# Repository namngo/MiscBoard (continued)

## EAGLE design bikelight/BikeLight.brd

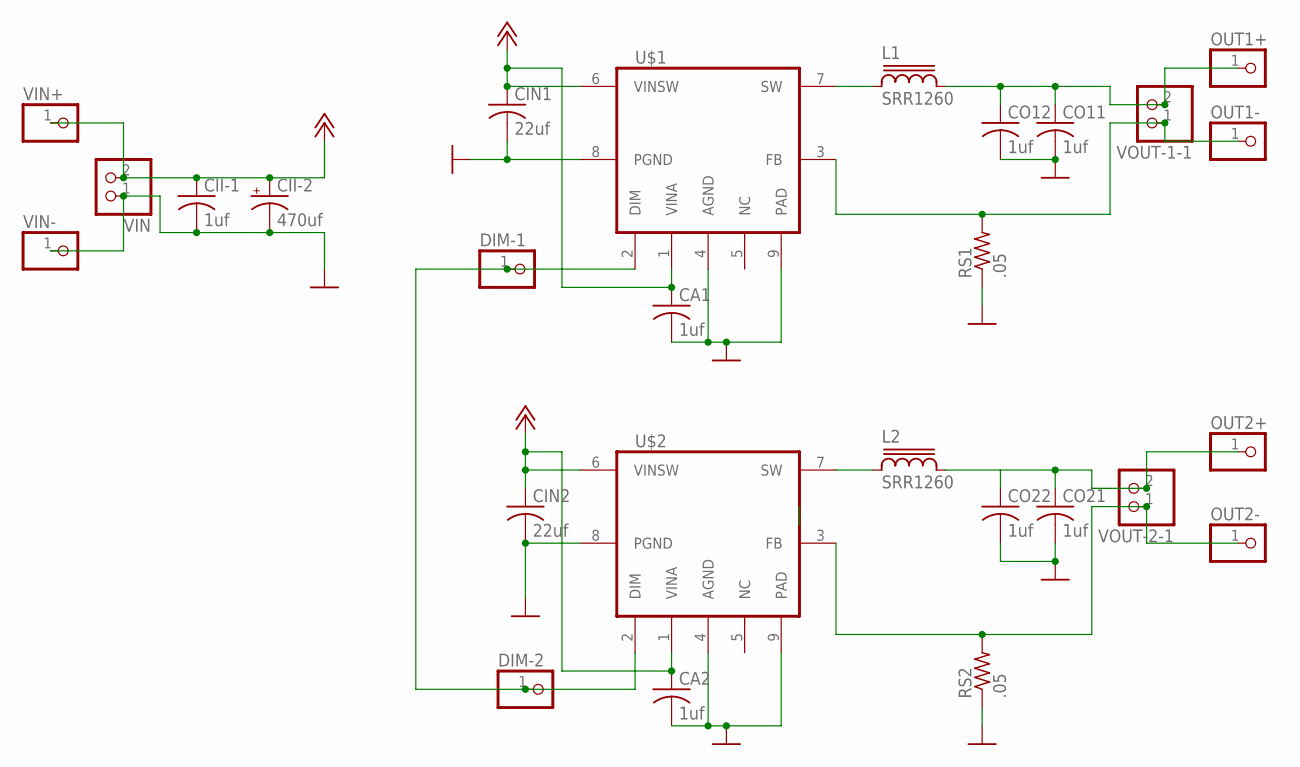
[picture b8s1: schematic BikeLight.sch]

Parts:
CA1, CA2: 1uf; C1210
CII-1: 1uf; C1210
CII-2: 470uf; UD-10X10_NICHICON
CIN1, CIN2: 22uf; C1210
CO11, CO12, CO21, CO22: 1uf; C1210
DIM-1, DIM-2: PINHD-1X1; 1X01
L1, L2: SRR1260
OUT1+, OUT1-, OUT2+, OUT2-: PINHD-1X1; 1X01
RS1, RS2: .05; R1206
U$1, U$2: LED2001PHR; SOIC127P600X170-9N
VIN: PINHD-1X2; 1X02
VIN+: PINHD-1X1; 1X01
VIN-: PINHD-1X1; 1X01
VOUT-1-1, VOUT-2-1: PINHD-1X2; 1X02

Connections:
+12V: CA1.1, CA2.1, CII-1.1, CII-2.+, CIN1.1, CIN2.1, U$1.1 (VINA), U$1.6 (VINSW), U$2.1 (VINA), U$2.6 (VINSW), VIN.2, VIN+.1
GND: CA1.2, CA2.2, CII-1.2, CII-2.-, CIN1.2, CIN2.2, CO11.2, CO12.2, CO21.2, CO22.2, RS1.1, RS2.1, U$1.4 (AGND), U$1.8 (PGND), U$1.9 (PAD), U$2.4 (AGND), U$2.8 (PGND), U$2.9 (PAD), VIN.1, VIN-.1
unnamed: DIM-1.1, DIM-2.1, U$1.2 (DIM), U$2.2 (DIM)
unnamed: L1.1, U$1.7 (SW)
unnamed: L2.1, U$2.7 (SW)
N-OUT-1-N: OUT1-.1, RS1.2, U$1.3 (FB), VOUT-1-1.1
N-OUT-1-P: CO11.1, CO12.1, L1.2, OUT1+.1, VOUT-1-1.2
N-OUT-2-N: OUT2-.1, RS2.2, U$2.3 (FB), VOUT-2-1.1
N-OUT-2-P: CO21.1, CO22.1, L2.2, OUT2+.1, VOUT-2-1.2

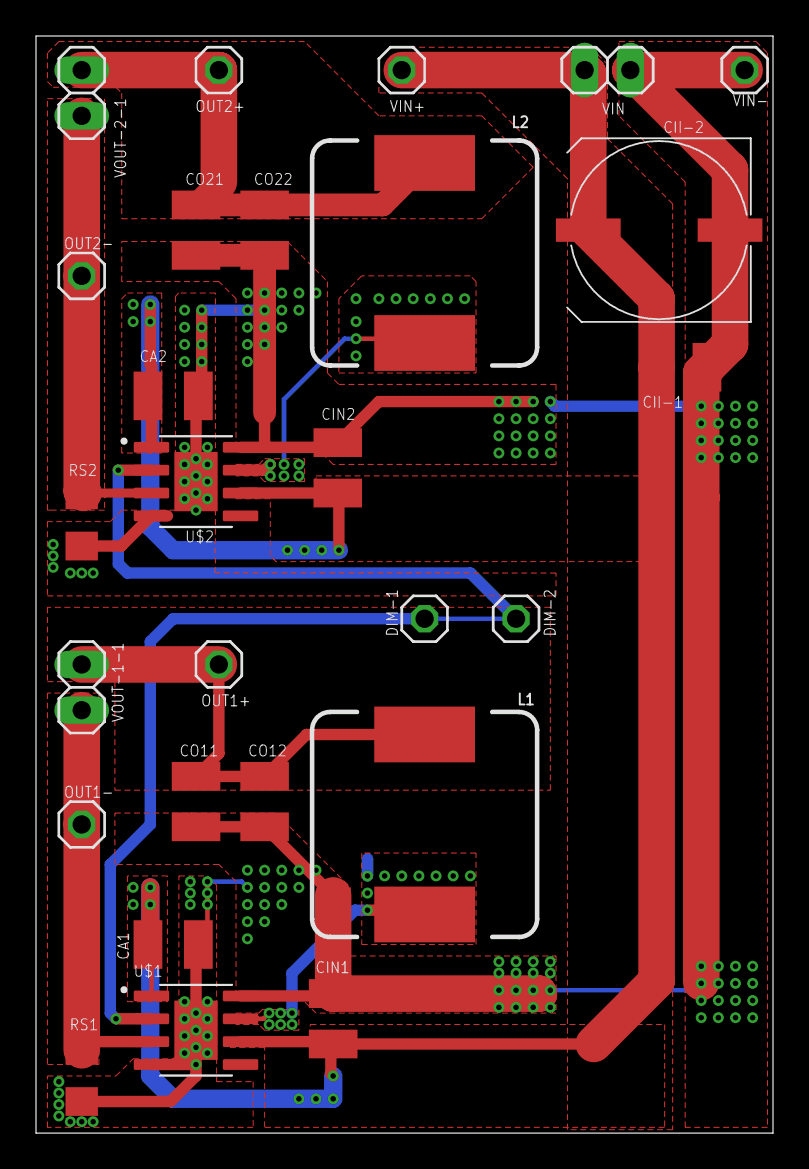
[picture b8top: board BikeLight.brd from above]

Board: 2 copper layers, 40.9 x 61.0 mm, 27 parts (0 on the bottom side), 9 nets.

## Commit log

2019-11-27 initial
2019-12-02 change discretesemi
2019-12-02 update electric board
2019-12-02 basic
2019-12-02 finish basic design
2019-12-02 finish designing boards
2019-12-03 move board up
2019-12-03 done design board
2019-12-04 use standard parts
2019-12-04 use new standard parts
2019-12-07 add inductor library
2019-12-18 move bikelight to this
2019-12-18 add unedit footprint
2019-12-24 redesign the board
2019-12-24 remove unused files
2019-12-24 update gitignore for library
2020-01-12 elec loads
2020-02-03 redesign
2020-02-03 led2001
2020-02-09 change
2020-02-10 nearly done
2020-02-11 bikelight:
2020-02-13 finish board light sematic
2020-02-17 add new boards
2020-02-18 add esp32 comp
2020-02-21 esp32
2020-02-21 done
2020-02-22 eagle
2020-02-24 remove
2020-02-24 esp-comp
2020-02-24 done comp
2020-02-25 board
2020-02-25 add programmer board
2020-02-27 done board
2020-03-05 module
2020-03-07 bike
2020-03-12 atmel
2020-03-13 atmel arm
2020-03-16 layer sets
2020-03-16 move ic, error
2020-03-17 done sensor
2020-03-17 remove board
2020-03-17 output all boards
2020-03-18 ignore secret
2020-03-18 connecting to ada io
2020-03-18 settings
2020-03-18 done_ada
2020-03-18 done logging
2020-03-18 Done print serial
2020-03-19 done temp and serial
2020-03-19 add c# program to print out ip to serial
2020-03-19 vscode settings
2020-03-31 move bike board to bikelight repo
2020-04-04 debuging
2020-04-04 add stuff
2023-01-19 add new car lights
2023-02-06 designing new board
2023-02-06 almost finish
2023-02-06 finish v2 of power picker
2023-02-14 add new ina board
2023-02-17 add power jack
2023-02-21 powermetter_board
2023-02-23 adding sense resistor
2023-02-27 finish schematic, creating board
2023-02-27 finish basic positioning power board
2023-02-27 finish working on sunday
2023-03-02 routing
2023-03-07 redesigning
